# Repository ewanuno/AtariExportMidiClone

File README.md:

# AtariExportMidiClone
 a clone of the clab export midi interface for the atari ST

 there are some errors in this project, do not build pcbs from it untill they are resolved:

din5 footprints connected incorrectly.

maybe others too...

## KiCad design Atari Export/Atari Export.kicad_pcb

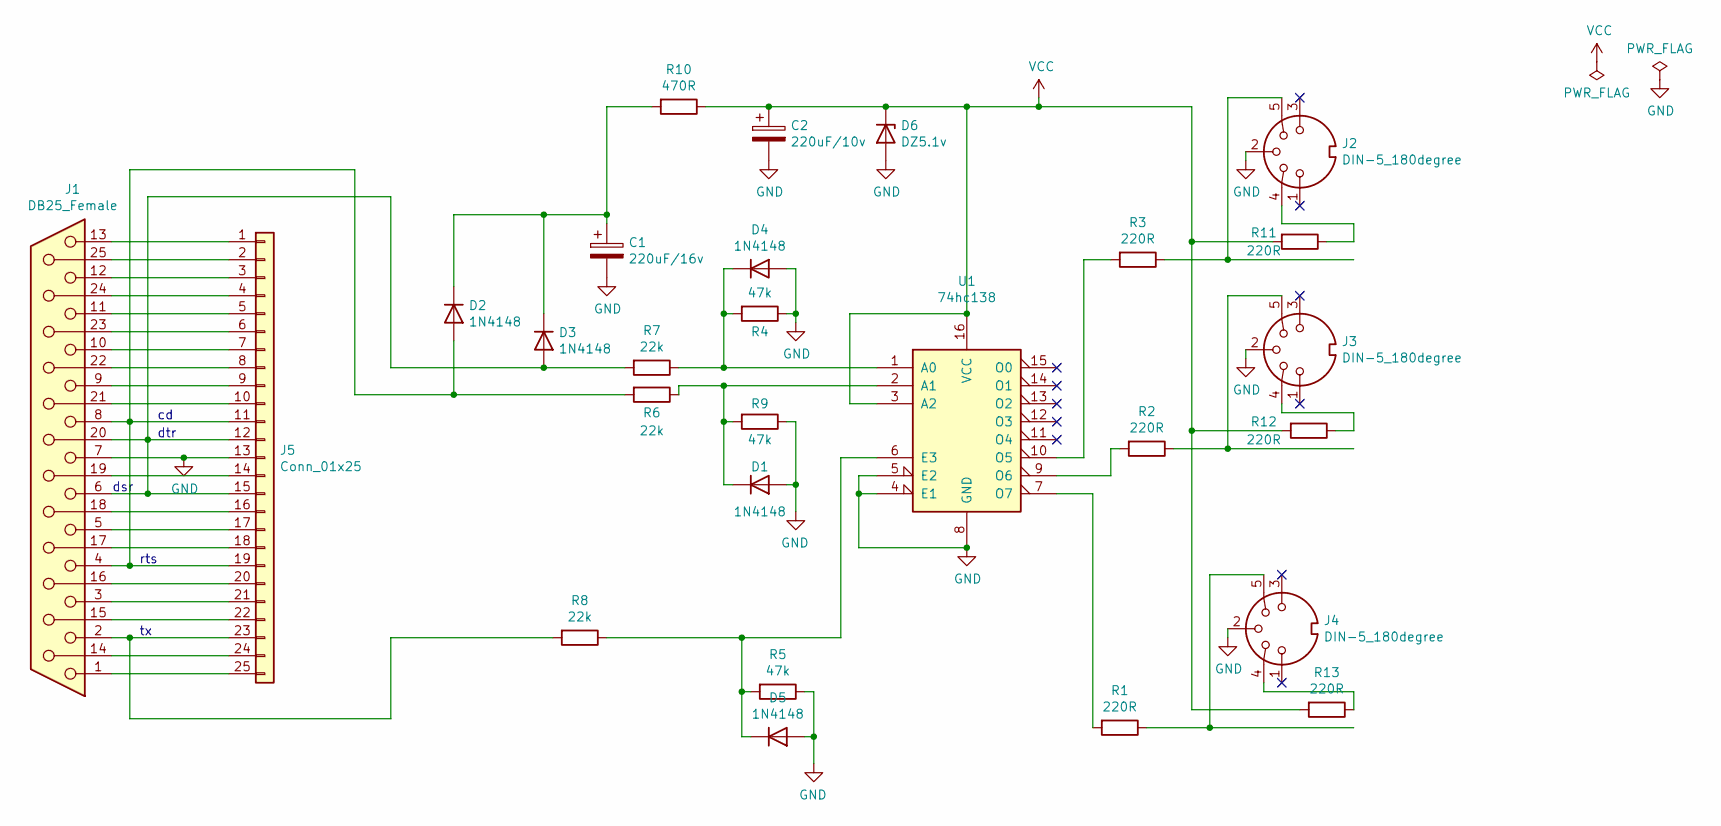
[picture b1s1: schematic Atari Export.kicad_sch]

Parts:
C1: 220uF/16v; CP_Elec_6.3x7.7; LCSC C182267
C2: 220uF/10v; CP_Elec_6.3x7.7; LCSC C182267
D1, D2, D3, D4, D5: 1N4148; D_SOD-323F; LCSC C2128
D6: DZ5.1v; D_SOD-523; LCSC C84996
J1: DB25_Female; DSUB-25_Female_Horizontal_P2.77x2.84mm_EdgePinOffset4.94mm_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; LCSC C698340
J2, J3, J4: DIN-5_180degree; SWITCHCRAFT_61PC5F_DIN5
J5: Conn_01x25; PinHeader_2x13_P2.54mm_Vertical
R1, R2, R3, R11, R12, R13: 220R; R_0603_1608Metric_Pad0.98x0.95mm_HandSolder; LCSC C4190
R4, R5, R9: 47k; R_0603_1608Metric_Pad0.98x0.95mm_HandSolder; LCSC C25819
R6, R7, R8: 22k; R_0603_1608Metric_Pad0.98x0.95mm_HandSolder; LCSC C31850
R10: 470R; R_0603_1608Metric_Pad0.98x0.95mm_HandSolder; LCSC C23179
U1: 74hc138; SOIC-16_3.9x9.9mm_P1.27mm; LCSC C5602

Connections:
GND: C1.2, C2.2, D1.2 (A), D4.2 (A), D5.2 (A), D6.2 (A), J1.7, J2.2, J3.2, J4.2, J5.13, R4.1, R5.1, R9.1, U1.4 (E1), U1.5 (E2), U1.8 (GND)
unnamed: C1.1, D2.1 (K), D3.1 (K), R10.2
unnamed: D1.1 (K), R6.1, R9.2, U1.2 (A1)
unnamed: D2.2 (A), J1.4, J1.8, J5.11, J5.19, R6.2
unnamed: D3.2 (A), J1.6, J1.20, J5.12, J5.15, R7.2
unnamed: D4.1 (K), R4.2, R7.1, U1.1 (A0)
unnamed: D5.1 (K), R5.2, R8.1, U1.6 (E3)
unnamed: J1.1, J5.25
unnamed: J1.2, J5.23, R8.2
unnamed: J1.3, J5.21
unnamed: J1.5, J5.17
unnamed: J1.9, J5.9
unnamed: J1.10, J5.7
unnamed: J1.11, J5.5
unnamed: J1.12, J5.3
unnamed: J1.13, J5.1
unnamed: J1.14, J5.24
unnamed: J1.15, J5.22
unnamed: J1.16, J5.20
unnamed: J1.17, J5.18
unnamed: J1.18, J5.16
unnamed: J1.19, J5.14
unnamed: J1.21, J5.10
unnamed: J1.22, J5.8
unnamed: J1.23, J5.6
unnamed: J1.24, J5.4
unnamed: J1.25, J5.2
unnamed: J2.4, R11.1
unnamed: J2.5, R3.1
unnamed: J3.4, R12.1
unnamed: J3.5, R2.1
unnamed: J4.4, R13.1
unnamed: J4.5, R1.1
unnamed: R1.2, U1.7 (O7)
unnamed: R2.2, U1.9 (O6)
unnamed: R3.2, U1.10 (O5)
VCC: C2.1, D6.1 (K), R10.1, R11.2, R12.2, R13.2, U1.3 (A2), U1.16 (VCC)

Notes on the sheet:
dtr
rts
dsr

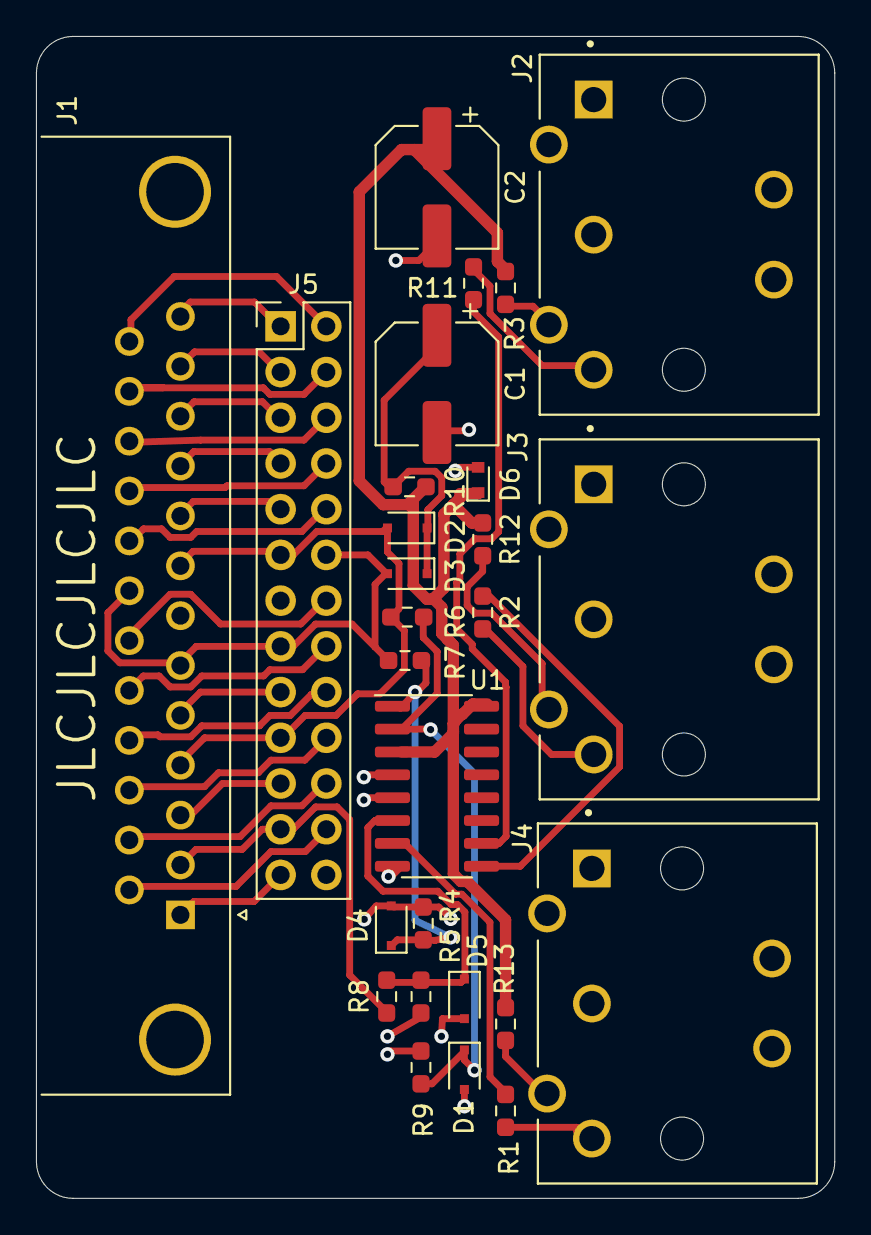
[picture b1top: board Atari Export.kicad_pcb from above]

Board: 2 copper layers, 44.3 x 64.5 mm, 27 parts (0 on the bottom side), 37 nets.

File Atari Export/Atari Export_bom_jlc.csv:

"Comment","Designator","Footprint","LCSC Part #"
"220uF/16v","C1","CP_Elec_6.3x7.7","C182267"
"220uF/10v","C2","CP_Elec_6.3x7.7","C182267"
"1N4148","D2,D3,D4,D1,D5","D_SOD-323F","C2128"
"DZ5.1v","D6","D_SOD-523","C84996"
"DB25_Female","J1","DSUB-25_Female_Horizontal_P2.77x2.84mm_EdgePinOffset4.94mm_Housed_MountingHolesOffset7.48mm","C698340"
"47k","R4,R9,R5","R_0603_1608Metric_Pad0.98x0.95mm_HandSolder","C25819"
"22k","R7,R6,R8","R_0603_1608Metric_Pad0.98x0.95mm_HandSolder","C31850"
"470R","R10","R_0603_1608Metric_Pad0.98x0.95mm_HandSolder","C23179"
"220R","R11,R12,R13,R3,R2,R1","R_0603_1608Metric_Pad0.98x0.95mm_HandSolder","C4190"
"74hc138","U1","SOIC-16_3.9x9.9mm_P1.27mm","C5602"

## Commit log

2024-11-29 initial comit
    movig the project to git,
    it is currently not in a working state, so don't build these boards yet!
2024-11-30 remove some extra files
2024-11-30 removed more stuff
    removed more stuff
2024-12-03 Update README.md
    add a warning that there are errors lurking and that this pcb is NOT ready for production.
